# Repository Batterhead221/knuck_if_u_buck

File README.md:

# knuck_if_u_buck (12v→5v_buck_converter)

Custom LMR51430 buck converter PCB (12V → 5V @ ~0.5A, designed with ~1A headroom).

CONCEPT DESIGN - WILL NOT FAB

Key features
	•	Optimized SW node geometry
	•	Tight input loop placement (VIN decoupling kept close)
	•	Clean feedback routing with isolation from noisy nodes
	•	Short switching loops for better EMI behavior
	•	Clear grounding strategy (return paths kept compact)
	•	Debug-friendly access (VIN, SW, FB, EN, 5V)

Hardware design
	•	Converter: TI LMR51430
	•	Input: 12V
	•	Output: 5V (target 0.5A, with ~1A headroom)
	•	Inductor: 6.8µH power inductor (500 kHz design choice)
	•	Feedback divider: 100k / 13.7k (sets 5V output)
	•	Output caps: 2×22µF + local decoupling
	•	Input caps: 22µF + 0.1µF placed close to VIN/GND 

Layout priorities
	•	Tight high-current loop: VIN → SW → L → COUT → GND
	•	Keep SW copper small (short + compact)
	•	Solid ground reference near power stage

Early project for learning and and gaining a better understanding of a buck converter.

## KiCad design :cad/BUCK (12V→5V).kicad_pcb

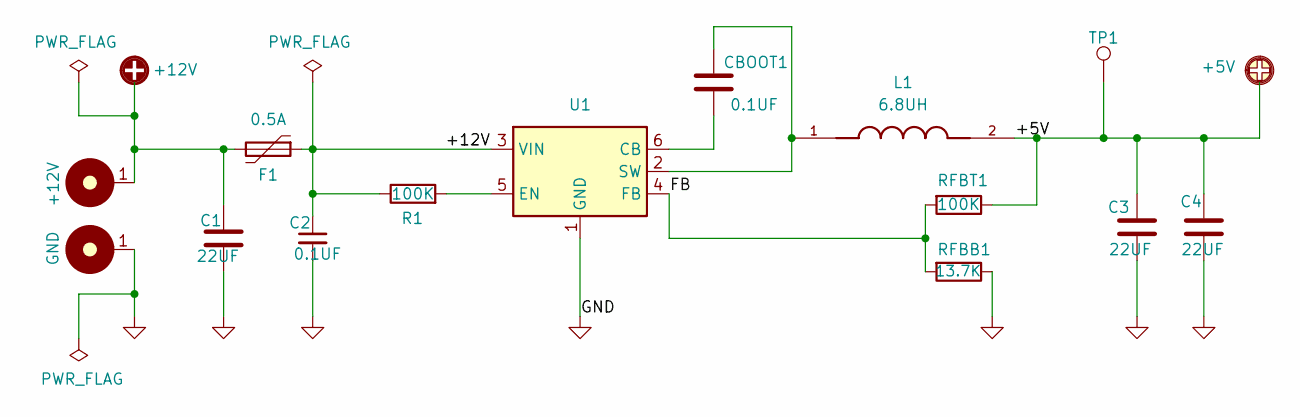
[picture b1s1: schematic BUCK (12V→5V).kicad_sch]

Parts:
C1, C3, C4: 22UF; C_0402_1005Metric_Pad0.74x0.62mm_HandSolder
C2: 0.1UF; C_0402_1005Metric_Pad0.74x0.62mm_HandSolder
CBOOT1: 0.1UF; C_0402_1005Metric_Pad0.74x0.62mm_HandSolder
F1: 0.5A; Fuse_0603_1608Metric; MPN JB06S5000R; LCSC C207014
H1: +12V; MountingHole_3.2mm_Pad
H2: GND; MountingHole_3.2mm_Pad
L1: 6.8UH; L_Coilcraft_XAL5030-XXX; PARTREV N/A
R1: 100K; R_0402_1005Metric_Pad0.72x0.64mm_HandSolder
RFBB1: 13.7K; R_0402_1005Metric_Pad0.72x0.64mm_HandSolder
RFBT1: 100K; R_0402_1005Metric_Pad0.72x0.64mm_HandSolder
TP1: 0.5mm; TestPoint-0.5mm
U1: LMR51430; SOT-23-6; MPN LMR51430XDDCR

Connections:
+12V: C1.2, C2.1, F1.1, F1.2, H1.1, R1.1, U1.3 (VIN)
/+5V: C3.2, C4.2, L1.2, RFBT1.1, TP1.1
/FB: RFBB1.2, RFBT1.2, U1.4 (FB)
GND: C1.1, C2.2, C3.1, C4.1, H2.1, RFBB1.1, U1.1 (GND)
unnamed: CBOOT1.1, U1.6 (CB)
unnamed: R1.2, U1.5 (EN)
unnamed: CBOOT1.2, L1.1, U1.2 (SW)

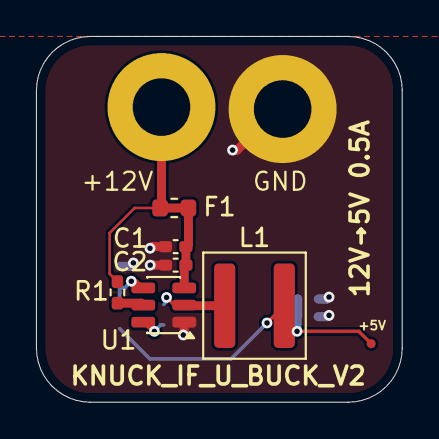
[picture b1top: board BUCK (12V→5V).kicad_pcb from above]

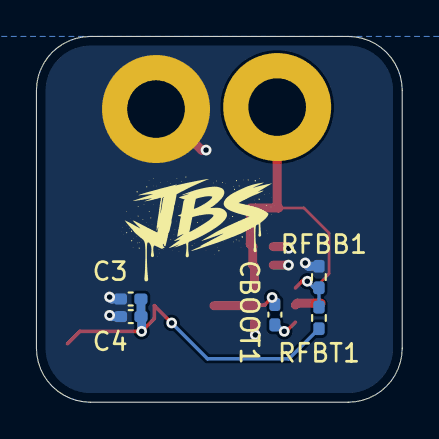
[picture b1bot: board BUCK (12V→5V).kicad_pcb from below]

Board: 2 copper layers, 20.3 x 20.3 mm, 14 parts (5 on the bottom side), 7 nets.

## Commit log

2026-04-18 file path restructure
2026-05-03 folder restructure
2026-05-13 Revised repo
